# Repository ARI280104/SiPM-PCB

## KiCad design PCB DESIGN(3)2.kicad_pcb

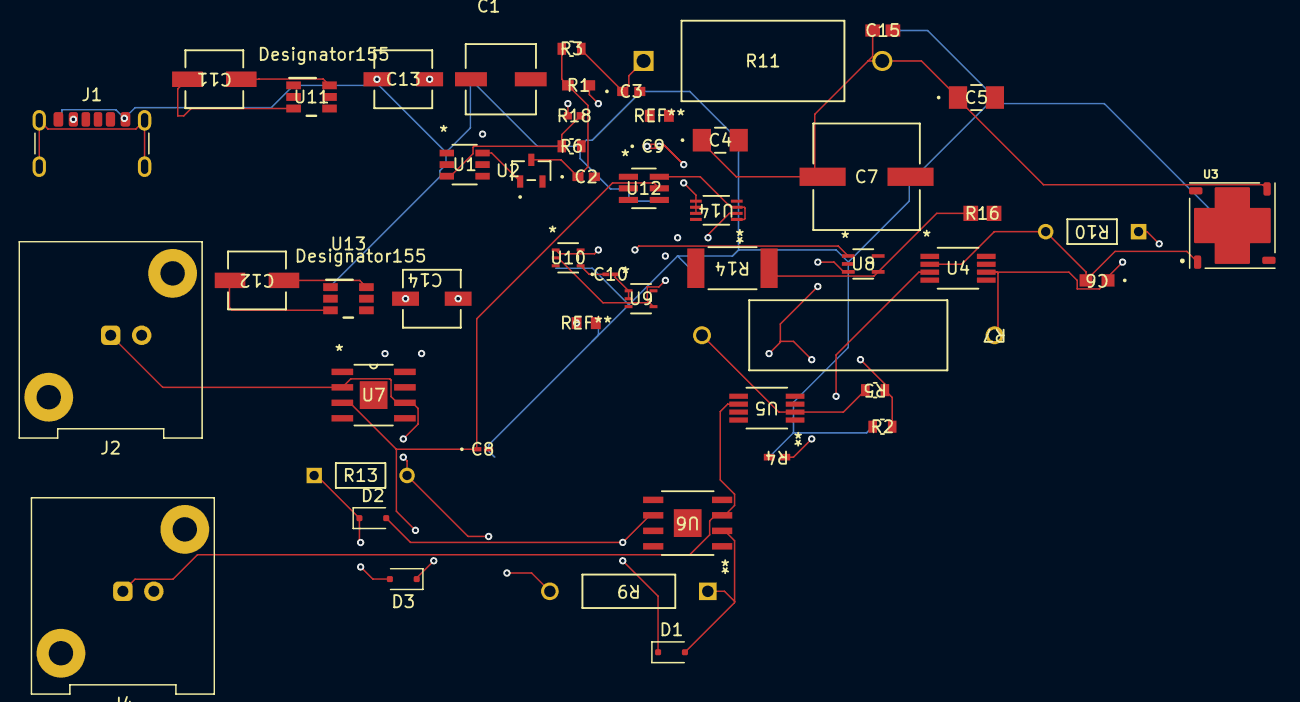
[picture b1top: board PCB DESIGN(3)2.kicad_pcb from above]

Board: 4 copper layers, 49 parts (0 on the bottom side), 31 nets.

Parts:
C1: EEE-FK1V220R; CAP_EEFK_C_PAN
C2: GRM155R60J475ME87D; CAP_GRM15-5_MUR-M
C3: GRM155R60J106ME05D; CAP_GRM155R60J106ME05D_MUR-M
C4, C5: ECH-U1H103GX5; CAP_H2_PAN-M
C6: 06031A100JAT2A; CAP_0603G_AVX-M
C7: EEE-FK1H101P; CAP_8 X 10.2_PAN
C8, C9: GRM0335C1E100JA01D; G-033_MUR-M
C10: GRM0335C1E100JA01D; G-033_MUR
C11, C12: EEE-1HA3R3SR; CAP_EEE_B_PAN-M
C13, C14: EEE-1HA3R3SR; CAP_EEE_B_PAN
C15: C0603C510J5GACTU; CAPC17595_87N_KEM-M
D1, D2, D3: BAT54J; D_SOD-323F
J1: USB_C_Receptacle_PowerOnly_6P; USB_C_Receptacle_GCT_USB4125-xx-x-0190_6P_TopMnt_Horizontal
J2, J4: Conn_Coaxial_Small; BNC_Amphenol_031-5539_Vertical
R1: ERJ-3EKF2002V; RC0603N_PAN-M
R2, R5, R6: CRG0603F10K; RES0603_CRG_TYCO_TYC-M
R3: CRG0603F100K; RES0603_CRG_TYCO_TYC-M
R4: ERJ-2GEJ202X; RC0402N_PAN-M
R7: ROX3SJ10R; res2_1-1625892-1_TEC
R9: CMF552K2300BHEB; RES_CMF07_VIS
R10, R13: RNC50J1341BSB14; ERC50_VIS
R11: UPW50B500RV; RES_UPW50_TYCO_TYC
R14: ERJ-1TYJ202U; RC2512N_PAN-M
R16: ERJ-6GEYJ204V; RC0805N_PAN-M
R18: CRG0402F20K; RES0402_CRG_TYCO_TYC-M
U1: MAX5025EUT+T; 21-0058I_MXM-M
U2: ZHCS500TA; SOT23_2P9X1P3_DIO-L
U3: MICROFC-60035-SMT-TR1; XDCR_MICROFC-60035-SMT-TR1
U4, U5: OPA695IDGKT; DGK8-M
U6: OPA354AIDDA; DDA8_2P28X2P28-M
U7: OPA354AIDDA; DDA8_2P28X2P28
U8: TLV3601QDCKRQ1; SC70-5_DCK_TEX-M
U9, U10: SN74AHC1G00DCKR; DCK5-L
U11, U13: LM2664M6X/NOPB; DBV0006A_M
U12: ADG1201BRJZ-REEL7; RJ_6_ADI-M
U14: SN74LVC2G02DCUR; DCU8_TEX-M

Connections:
5V_VCC: C1.1, J1.A9 (VBUS), J1.B9 (VBUS), R16.2, U1.4 (*SHDN), U1.5 (VCC), U4.7 (VS+), U5.7 (VS+), U6.7 (V+), U7.7 (V+), U8.5 (VCC), U9.5 (VCC), U10.5 (VCC), U11.5 (V+), U12.1 (VDD), U13.5 (V+), U14.8 (VCC)
-5V_VEE1: C13.1, U4.4 (VS-), U5.4 (VS-)
-5V_VEE2: C14.1, U6.4 (V-), U7.4 (V-)
GND: C1.2, C2.2, C3.2, C4.2, C5.2, C7.2, C8.2, C15.2, J1.A12 (GND), J1.B12 (GND), R2.1, R4.2, R6.2, R14.2, U1.1 (PGND), U1.2 (GND), U3.5 (EP), U5.3 (NONINVERTINGINPUT), U8.2 (VEE), U9.3 (GND), U10.3 (GND), U11.1 (GND), U12.2 (GND), U12.3 (VSS), U12.4 (S), U13.1 (GND), U14.4 (GND)
unnamed: C2.1, R1.1, R3.1, U2.3
unnamed: C3.1, R3.2, R11.1
unnamed: C4.1, C5.1, C7.1, C15.1, R11.2, U3.3
unnamed: D1.2 (A), R9.1, U6.2 (IN-)
unnamed: D1.1 (K), D2.2 (A), U6.6 (OUT)
unnamed: D2.1 (K), D3.2 (A), R13.1
unnamed: C8.1, D3.1 (K), U7.3 (IN+), U12.5 (D)
unnamed: J2.1 (In), R9.2, R13.2, U7.2 (IN-), U7.6 (OUT)
unnamed: J4.1 (In), R2.2, R5.1, U5.6 (OUTPUT), U6.3 (IN+), U8.3 (IN+)
unnamed: R1.2, R18.1
unnamed: R6.1, R18.2, U1.3 (FB)
unnamed: U1.6 (LX), U2.1
unnamed: C6.2, R10.2, U3.1, U4.2 (INVERTINGINPUT)
unnamed: R4.1, U4.3 (NONINVERTINGINPUT)
unnamed: C6.1, R7.1, R10.1, U4.6 (OUTPUT)
unnamed: R5.2, R7.2, U5.2 (INVERTINGINPUT)
unnamed: R14.1, R16.1, U8.4 (IN-)
unnamed: C10.2, U9.1 (A), U9.2 (B)
unnamed: U8.1 (OUT), U10.1 (A)
unnamed: U9.4 (Y), U10.2 (B), U14.2 (1B)
unnamed: C10.1, U10.4 (Y)
unnamed: C11.1, U11.6 (CAP+)
unnamed: C11.2, U11.3 (CAP-)
unnamed: U12.6 (IN), U14.1 (1A), U14.3 (2Y)
unnamed: C12.1, U13.6 (CAP+)
unnamed: C12.2, U13.3 (CAP-)
unnamed: C9.1, C9.2, U14.5 (2A), U14.6 (2B), U14.7 (1Y)
